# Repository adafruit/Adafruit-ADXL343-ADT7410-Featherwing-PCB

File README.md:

# Adafruit-ADXL353-ADT7410-Featherwing-PCB

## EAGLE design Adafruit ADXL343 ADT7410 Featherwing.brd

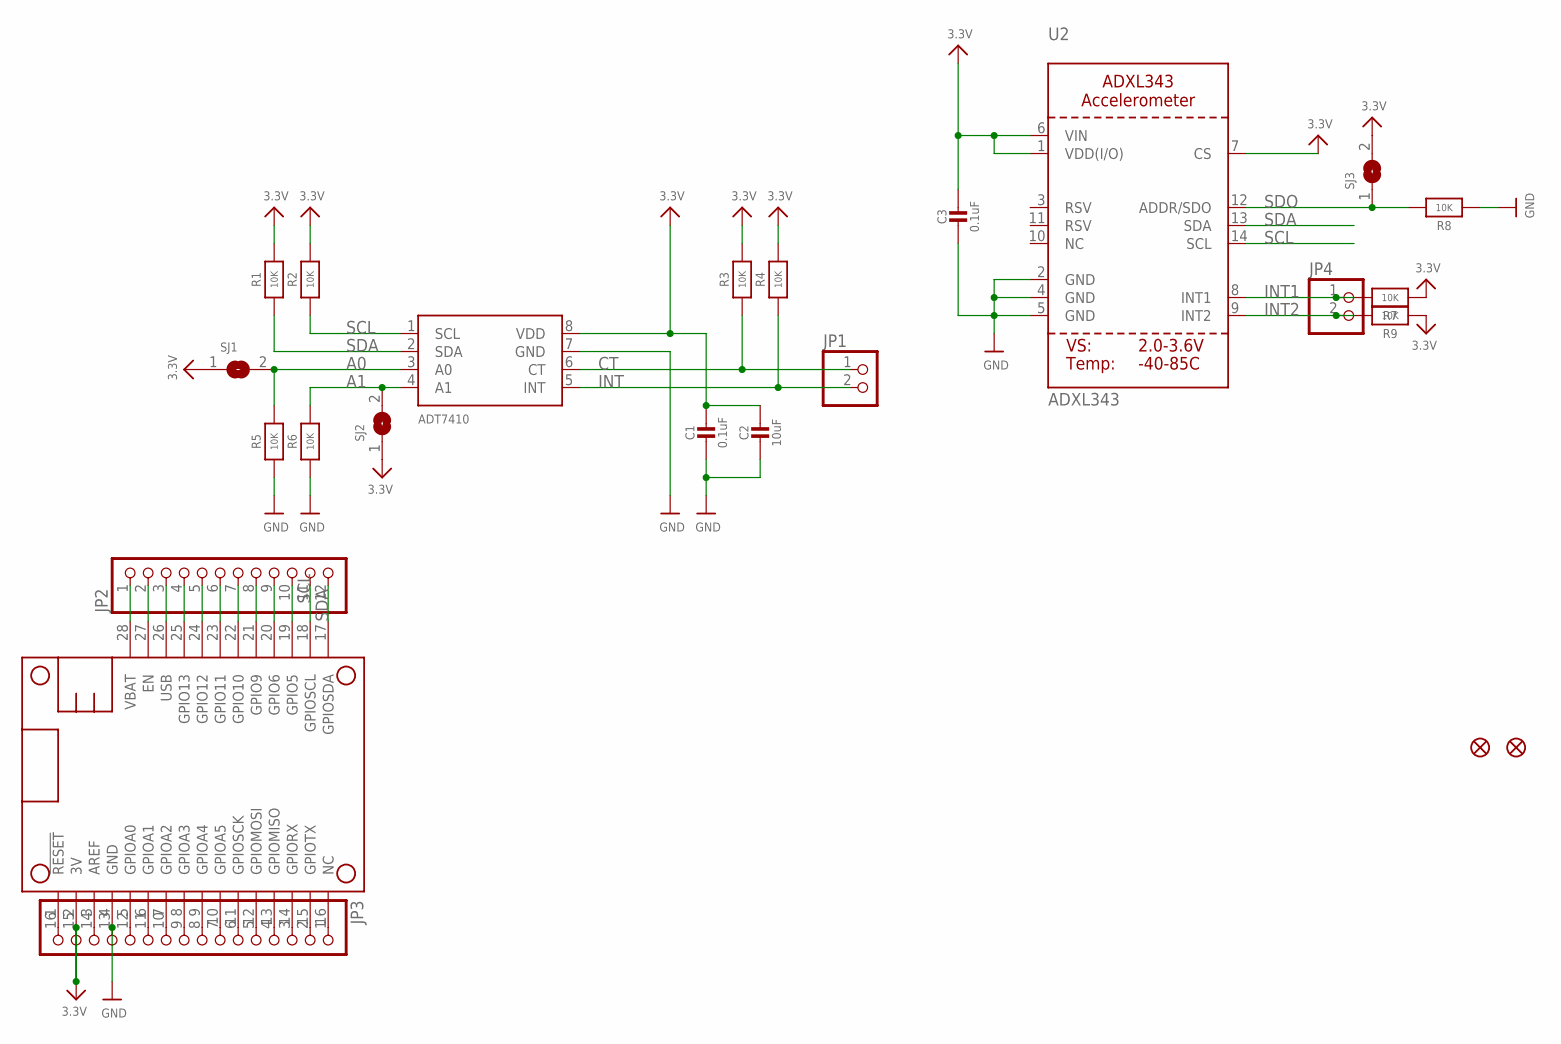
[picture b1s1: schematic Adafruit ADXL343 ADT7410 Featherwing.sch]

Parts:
C1, C3: 0.1uF; 0603-NO
C2: 10uF; 0805-NO
FID1, FID2: FIDUCIAL_1MM
JP1, JP4: HEADER-1X2ROUND; 1X02_ROUND
JP2: HEADER-1X1276MIL; 1X12_ROUND_76MIL
JP3: HEADER-1X16_76MIL; 1X16_ROUND_76MIL
MS1: FEATHERWING
R1, R2, R3, R4, R5, R6, R7, R8, R9: 10K; 0603-NO
SJ1, SJ2, SJ3: SOLDERJUMPER; SOLDERJUMPER_ARROW_NOPASTE
U1: ADT7410; SOIC8_150MIL
U2: ADXL343; LGA14

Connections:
3.3V: C1.1, C2.1, C3.1, JP3.15, MS1.2 (3V), R1.2, R2.2, R3.2, R4.2, R7.1, R9.1, SJ1.1, SJ2.1, SJ3.2, U1.8 (VDD), U2.1 (VDD(I/O)), U2.6 (VIN), U2.7 (CS)
A0: R5.2, SJ1.2, U1.3 (A0)
A1: R6.2, SJ2.2, U1.4 (A1)
CT: JP1.1, R3.1, U1.6 (CT)
GND: C1.2, C2.2, C3.2, JP3.13, MS1.4 (GND), R5.1, R6.1, R8.1, U1.7 (GND), U2.2 (GND), U2.4 (GND), U2.5 (GND)
INT: JP1.2, R4.1, U1.5 (INT)
INT1: JP4.1, R7.2, U2.8 (INT1)
INT2: JP4.2, R9.2, U2.9 (INT2)
unnamed: JP2.2, MS1.27 (EN)
unnamed: JP2.4, MS1.25 (GPIO13)
unnamed: JP2.5, MS1.24 (GPIO12)
unnamed: JP2.6, MS1.23 (GPIO11)
unnamed: JP2.7, MS1.22 (GPIO10)
unnamed: JP2.8, MS1.21 (GPIO9)
unnamed: JP2.9, MS1.20 (GPIO6)
unnamed: JP2.10, MS1.19 (GPIO5)
unnamed: JP3.1, MS1.16 (NC)
unnamed: JP3.2, MS1.15 (GPIOTX)
unnamed: JP3.3, MS1.14 (GPIORX)
unnamed: JP3.4, MS1.13 (GPIOMISO)
unnamed: JP3.5, MS1.12 (GPIOMOSI)
unnamed: JP3.6, MS1.11 (GPIOSCK)
unnamed: JP3.7, MS1.10 (GPIOA5)
unnamed: JP3.8, MS1.9 (GPIOA4)
unnamed: JP3.9, MS1.8 (GPIOA3)
unnamed: JP3.10, MS1.7 (GPIOA2)
unnamed: JP3.11, MS1.6 (GPIOA1)
unnamed: JP3.12, MS1.5 (GPIOA0)
unnamed: JP3.14, MS1.3 (AREF)
unnamed: JP3.16, MS1.1 (!RESET)
SCL: JP2.11, MS1.18 (GPIOSCL), R2.1, U1.1 (SCL), U2.14 (SCL)
SDA: JP2.12, MS1.17 (GPIOSDA), R1.1, U1.2 (SDA), U2.13 (SDA)
SDO: R8.2, SJ3.1, U2.12 (ADDR/SDO)
USB: JP2.3, MS1.26 (USB)
VBAT: JP2.1, MS1.28 (VBAT)

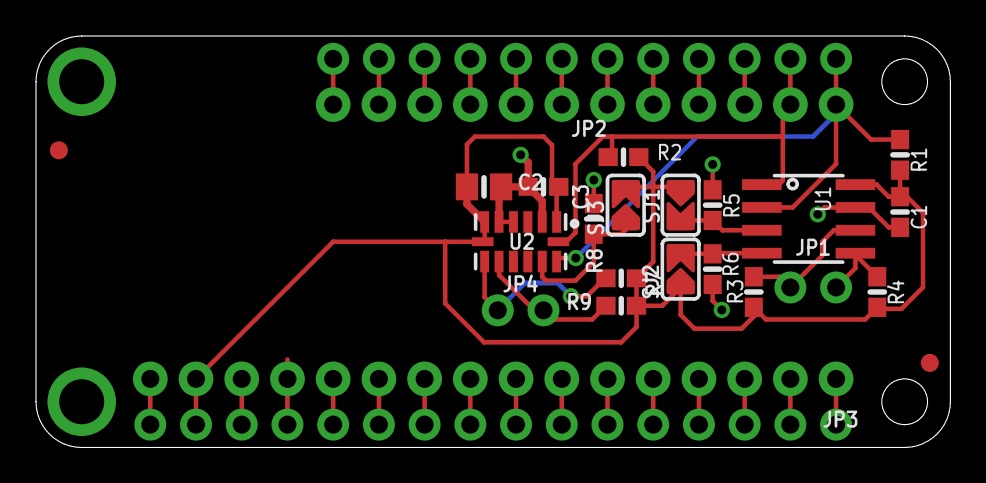
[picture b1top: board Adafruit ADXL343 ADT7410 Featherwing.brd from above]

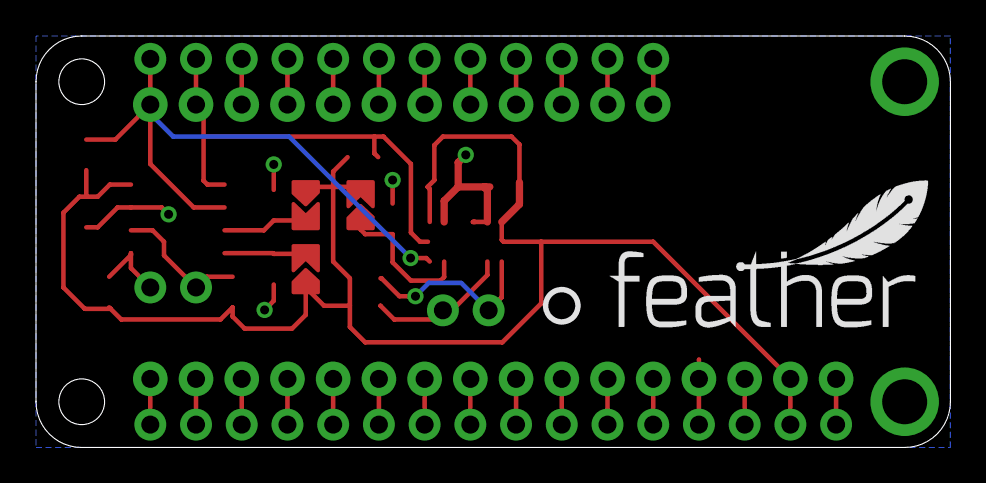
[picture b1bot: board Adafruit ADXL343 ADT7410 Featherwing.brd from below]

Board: 2 copper layers, 50.8 x 22.9 mm, 27 parts (2 on the bottom side), 35 nets.

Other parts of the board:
U$1: PCBFEAT-REV-040
U$23: FEATHERLOGO_MED
U$24: ADIWING_TOP

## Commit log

2019-11-22 init

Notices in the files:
parts and their libraries:
microbuilder: This work is placed in the public domain, and may be freely used for commercial and non-commercial work with the following conditions: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
